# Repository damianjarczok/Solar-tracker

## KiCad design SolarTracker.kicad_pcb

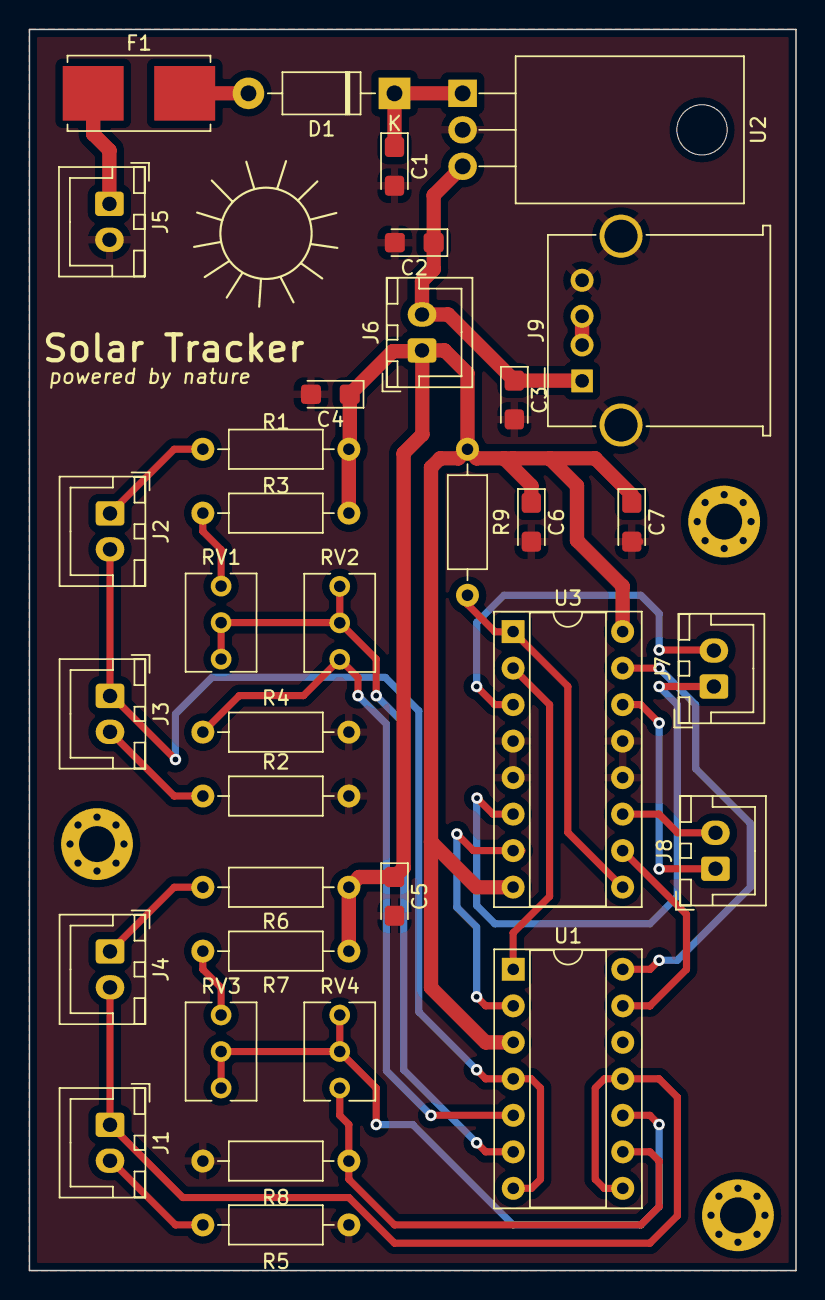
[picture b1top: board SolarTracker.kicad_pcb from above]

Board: 2 copper layers, 53.3 x 86.4 mm, 34 parts (0 on the bottom side), 28 nets.

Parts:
C1: 220n; CP_EIA-3216-18_Kemet-A
C2, C3, C4, C5, C6, C7: 100n; CP_EIA-3216-18_Kemet-A
D1: 1N4007; D_DO-41_SOD81_P10.16mm_Horizontal
F1: 2A; Fuseholder_Littelfuse_Nano2_154x
J1: LDR4; JST_XH_B2B-XH-A_1x02_P2.50mm_Vertical
J2: LDR1; JST_XH_B2B-XH-A_1x02_P2.50mm_Vertical
J3: LDR2; JST_XH_B2B-XH-A_1x02_P2.50mm_Vertical
J4: LDR3; JST_XH_B2B-XH-A_1x02_P2.50mm_Vertical
J5: PWR 9V - 30V Solar Cell; JST_XH_B2B-XH-A_1x02_P2.50mm_Vertical
J6: ON/OFF obrot; JST_XH_B2B-XH-A_1x02_P2.50mm_Vertical
J7: Motor1; JST_XH_B2B-XH-A_1x02_P2.50mm_Vertical
J8: Motor2; JST_XH_B2B-XH-A_1x02_P2.50mm_Vertical
J9: USB_A; USB_A_Molex_67643_Horizontal
R1, R2, R5, R6: 20k; R_Axial_DIN0207_L6.3mm_D2.5mm_P10.16mm_Horizontal
R3, R7, R9: 10k; R_Axial_DIN0207_L6.3mm_D2.5mm_P10.16mm_Horizontal
R4, R8: 33k; R_Axial_DIN0207_L6.3mm_D2.5mm_P10.16mm_Horizontal
RV1, RV3: 22k; Potentiometer_Vishay_T73XW_Horizontal
RV2, RV4: 10k; Potentiometer_Vishay_T73XW_Horizontal
U1: LM2901; DIP-14_W7.62mm_Socket
U2: LM7805_TO220; TO-220-3_Horizontal_TabDown
U3: L293D; DIP-16_W7.62mm_Socket

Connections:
GND: C1.2, C2.2, C3.2, C4.2, C5.2, C6.2, C7.2, J5.2, J9.4 (GND), J9.5 (Shield), R2.2, R4.2, R5.2, R8.2, U2.2 (GND), U3.4 (GND), U3.5 (GND), U3.12 (GND), U3.13 (GND)
unnamed: C1.1, D1.1 (K), U2.1 (VI)
unnamed: D1.2 (A), F1.2
unnamed: F1.1, J5.1
unnamed: J1.1, J4.2, U1.8 (-), U1.11 (+)
unnamed: J1.2, R5.1
unnamed: J2.1, R1.2
unnamed: J2.2, J3.1, U1.4 (-), U1.7 (+)
unnamed: J3.2, R2.1
unnamed: J4.1, R6.2
unnamed: J7.1, U3.6 (2Y)
unnamed: J7.2, U3.3 (1Y)
unnamed: J8.1, U3.14 (4Y)
unnamed: J8.2, U3.11 (3Y)
unnamed: J9.2 (D-), J9.3 (D+)
unnamed: R3.2, RV1.1
unnamed: R4.1, RV2.3, U1.5 (+)
unnamed: R7.2, RV3.1
unnamed: R8.1, RV4.3, U1.9 (+)
unnamed: R9.2, U3.1 (EN1,2), U3.9 (EN3,4)
unnamed: RV1.2, RV1.3, RV2.1, RV2.2, U1.6 (-)
unnamed: RV3.2, RV3.3, RV4.1, RV4.2, U1.10 (-)
unnamed: U1.1, U3.2 (1A)
unnamed: U1.2, U3.7 (2A)
unnamed: U1.13, U3.10 (3A)
unnamed: U1.14, U3.15 (4A)
unnamed: C2.1, C3.1, J6.2, J9.1 (VBUS), U2.3 (VO)
VCC: C4.1, C5.1, C6.1, C7.1, J6.1, R1.1, R3.1, R6.1, R7.1, R9.1, U3.8 (VCC2), U3.16 (VCC1)
